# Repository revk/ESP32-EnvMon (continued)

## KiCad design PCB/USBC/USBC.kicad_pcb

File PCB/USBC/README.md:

# USBC

These files are for use in [KiCad](https://www.kicad.org).

## Trademark

This is an open source project, but bear in mind you cannot sell boards bearing the Andrews & Arnold Ltd name, the A&A logo, the registered trademark AJK logo, or the GS1 allocated EANs assigned to Andrews & Arnold Ltd.

## Images

*Auto generated 2025-05-04T08:07:17*

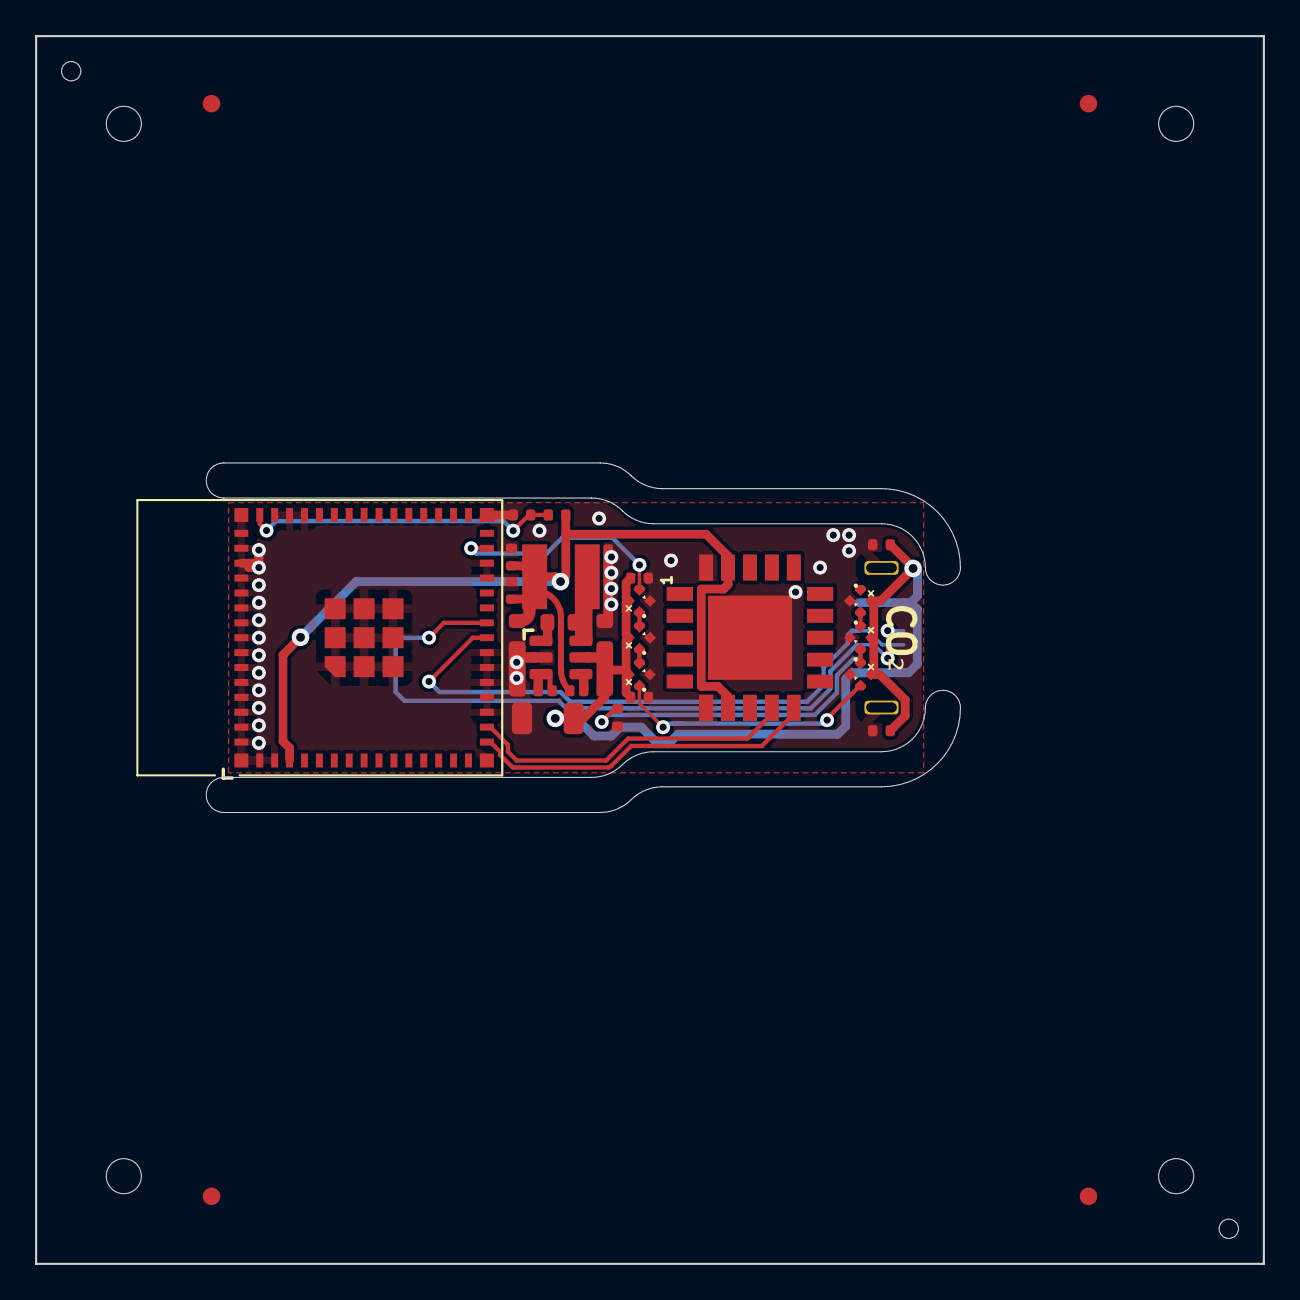
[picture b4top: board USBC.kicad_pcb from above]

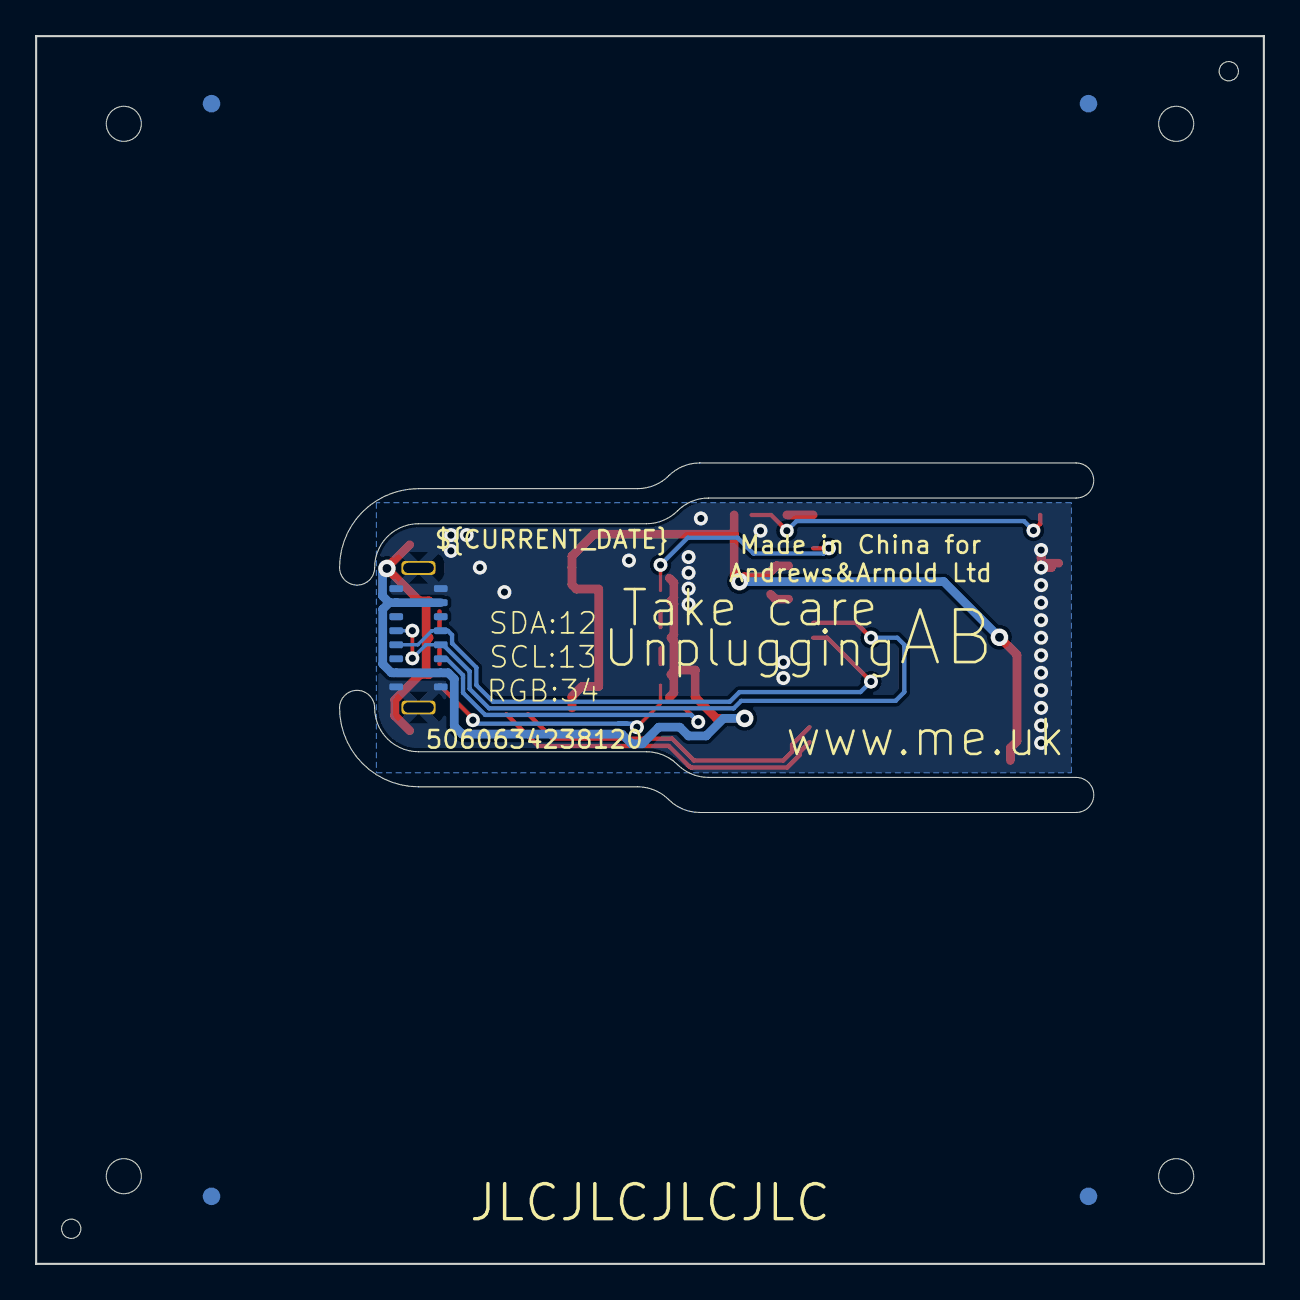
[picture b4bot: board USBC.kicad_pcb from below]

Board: 2 copper layers, 70.0 x 70.0 mm, 30 parts (2 on the bottom side), 15 nets.

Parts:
C1, C4, C5, C9, C11: 100nF; C_0402
C2: 22uF; C_0402
C3: 1uF; C_0402
C6: 10uF 35V; C_0603_
C7: 10uF 6.3V; C_0603_
C8: 100nF; C_0603_
C10: 100uF 6.3V; C_1206
D1, D2, D3, D4, D5, D6: XL-1010RGBC-WS2812B; SMD1010
J1: USB-C-Plug-V
L2: 10uH; L_4x4_
PCB1: 70x70; PCB7070
R1: 10K; R_0402
R2: 5K1; R_0402
R9: 124k; R_0402_
R10: 39k2; R_0402_
R11: 1M; R_0402_
U2: ESP32-S3-MINI-1
U3: SCD41-D-R1; SCD41
U5: MD8942; SOT-23-6-MD8942
V1, V2: 70; VCUT70N

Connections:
+3.3V: C1.1, C2.1, R1.1, U2.3 (3V3), U3.7 (VDD), U3.19 (VDDH), U5.8 (VOUT)
D+: J1.A6 (D+), J1.B6 (D+), U2.24 (GPIO20)
D-: J1.A7 (D-), J1.B7 (D-), U2.23 (GPIO19)
GND: C1.2, C2.2, C3.2, C4.2, C5.2, C9.2, C10.1, C11.2, D1.3 (-), D2.3 (-), D3.3 (-), D4.3 (-), D5.3 (-), D6.3 (-), J1.A1 (GND), J1.A12 (GND), J1.B1 (GND), J1.B12 (GND), J1.S1 (SHIELD), J1.S2 (SHIELD), R2.2, U2.1 (GND), U2.2 (GND), U2.18 (GPIO14), U2.19 (GPIO15), U2.20 (GPIO16), U2.21 (GPIO17), U2.22 (GPIO18), U2.27 (GPIO47), U2.28 (GPIO33), U2.42 (GND), U2.43 (GND), U2.44 (GPIO46), U2.46 (GND), U2.47 (GND), U2.48 (GND), U2.49 (GND), U2.50 (GND), U2.51 (GND), U2.52 (GND), U2.53 (GND), U2.54 (GND), U2.55 (GND), U2.56 (GND), U2.57 (GND), U2.58 (GND), U2.59 (GND), U2.60 (GND), U2.61 (GND), U2.62 (GND), U2.63 (GND), U2.64 (GND), U2.65 (GND), U3.6 (GND), U3.20 (GND), U3.21 (GND), U5.2 (GND), U5.7 (GND)
LED: D1.4 (I), U2.29 (GPIO34)
unnamed: D1.1 (O), D2.4 (I)
unnamed: D2.1 (O), D3.4 (I)
unnamed: D3.1 (O), D4.4 (I)
unnamed: D4.1 (O), D5.4 (I)
unnamed: D5.1 (O), D6.4 (I)
unnamed: J1.A5 (CC), R2.1
unnamed: C3.1, R1.2, U2.45 (EN)
SCL: U2.17 (GPIO13), U3.9 (SCL)
SDA: U2.16 (GPIO12), U3.10 (SDA)
VBUS: C4.1, C5.1, C9.1, C10.2, C11.1, D1.2 (+), D2.2 (+), D3.2 (+), D4.2 (+), D5.2 (+), D6.2 (+), J1.A4 (VBUS), J1.A9 (VBUS), J1.B4 (VBUS), J1.B9 (VBUS), U5.5 (VIN)

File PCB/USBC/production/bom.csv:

Designator,Footprint,Quantity,Value,LCSC Part #
"C1, C11, C4, C5, C9",C_0402,5,100nF,
C10,C_1206,1,100uF 6.3V,
C2,C_0402,1,22uF,
C3,C_0402,1,1uF,
C6,C_0603_,1,10uF 35V,C194427
C7,C_0603_,1,10uF 6.3V,C1691
C8,C_0603_,1,100nF,
"D1, D2, D3, D4, D5, D6",SMD1010,6,XL-1010RGBC-WS2812B,C5349953
J1,USB-C-Plug-V,1,USB-C-Plug-V,C399938
L2,L_4x4_,1,10uH,
R1,R_0402,1,10K,
R10,R_0402_,1,39k2,
R11,R_0402_,1,1M,
R2,R_0402,1,5K1,
R9,R_0402_,1,124k,
U2,ESP32-S3-MINI-1,1,ESP32-S3-MINI-1,C3013941
U3,SCD41,1,SCD41-D-R1,
U5,SOT-23-6-MD8942,1,MD8942,C2684786

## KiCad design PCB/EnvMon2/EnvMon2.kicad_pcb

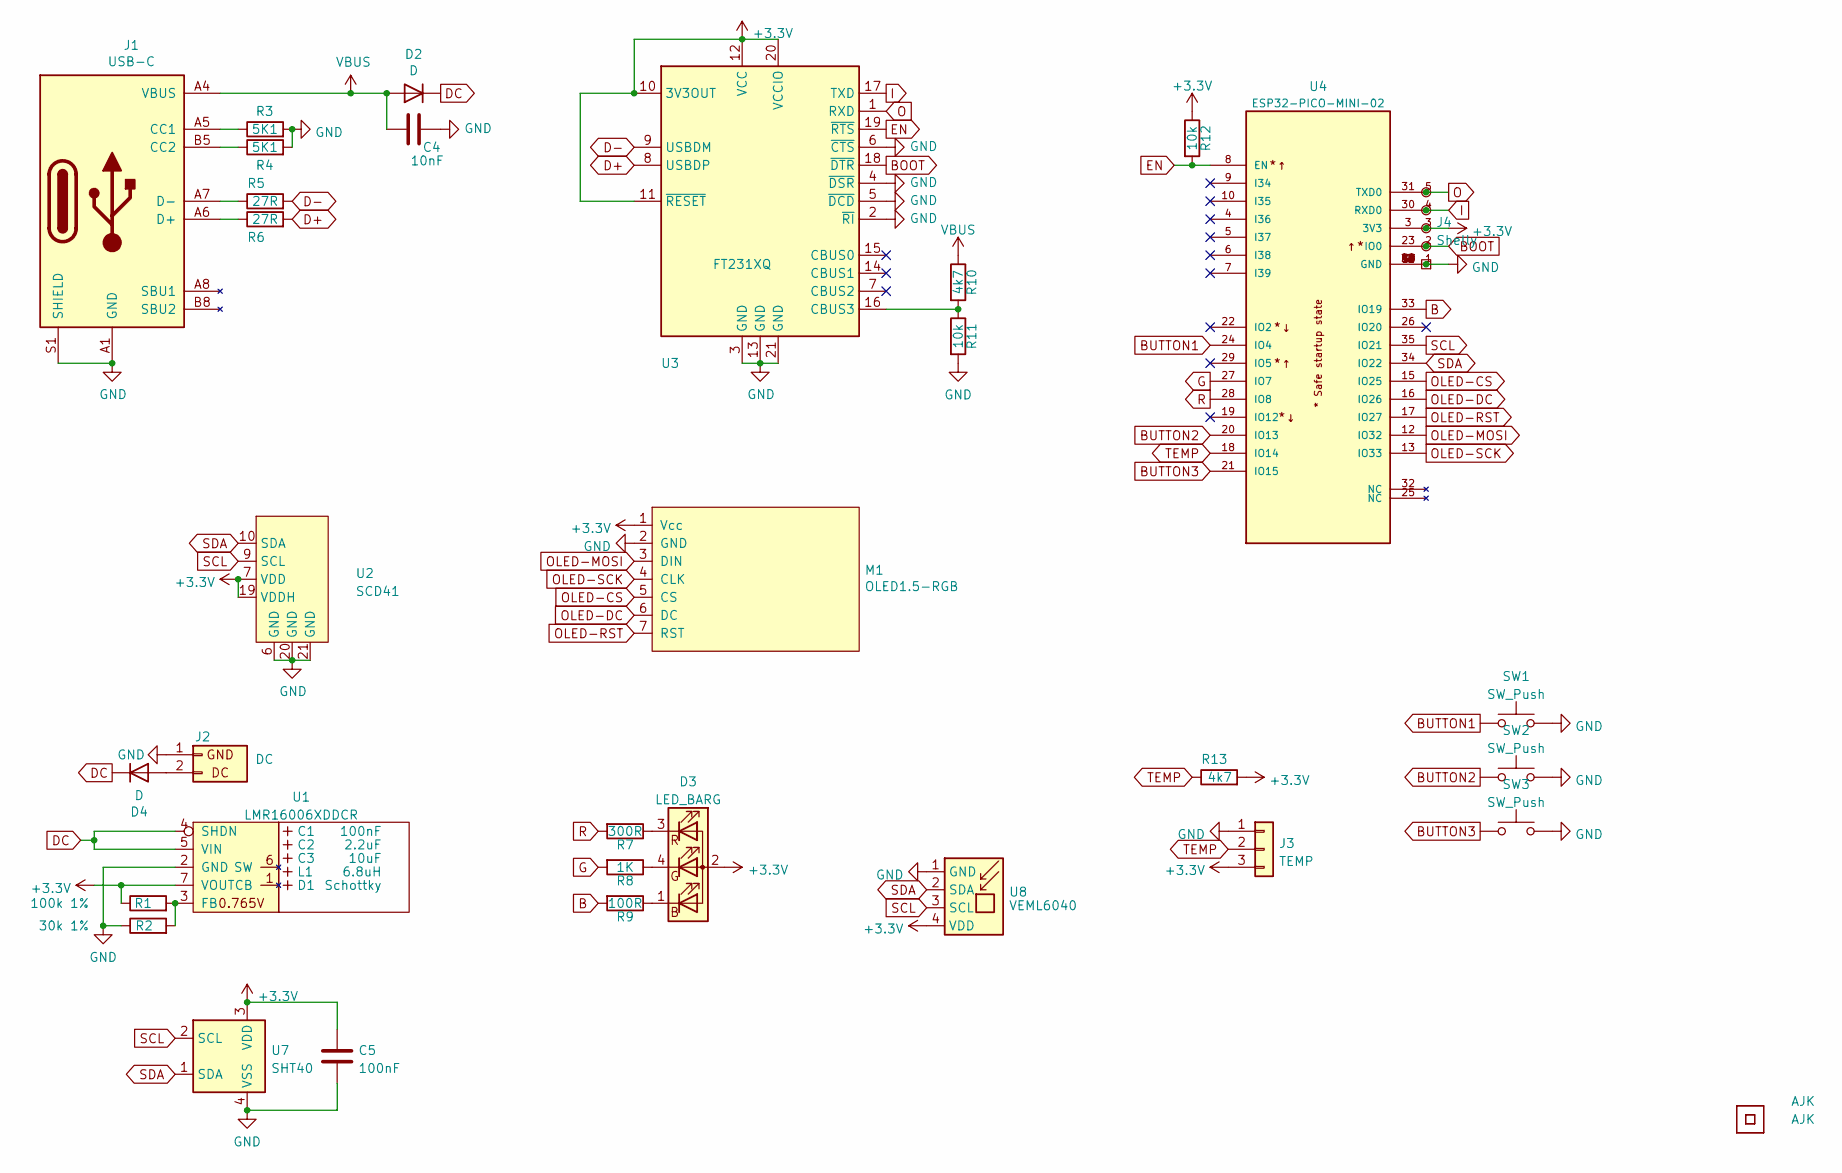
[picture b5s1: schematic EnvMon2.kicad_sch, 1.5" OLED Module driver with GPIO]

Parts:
C1: 100nF; C_0603_; LCSC Part # C30926
C2: 2.2uF; C_0805_; LCSC Part # C19110
C3: 10uF; C_0805_; LCSC Part # C17024
C4: 10nF; C_0603
C5: 100nF; C_0603
D1: Schottky; D_1206_; LCSC Part # C143805
D2, D4: D; D_1206; LCSC Part # C143805
D3: LED_BARG; MHS190RGBCT; LCSC Part # C409798
J1: USB-C; USC16-TR; LCSC Part # C709357
J2: DC; PTSM-HH-2-RA-W
J3: TEMP; PTSM-HH-3-RA
J4: Shelly
L1: 6.8uH; L_4x4_; LCSC Part # C354575
Logo1, Logo2: AJK
M1: OLED1.5-RGB
R1: 100k 1%; R_0603; LCSC Part # C14675
R2: 30k 1%; R_0603; LCSC Part # C100001
R3, R4: 5K1; R_0603
R5, R6: 27R; R_0603
R7: 300R; R_0603
R8: 1K; R_0603
R9: 100R; R_0603
R10, R13: 4k7; R_0603
R11, R12: 10k; R_0603
SW1, SW2, SW3: SW_Push; SW_PUSH_6mm_H13mm
U1: LMR16006XDDCR; SOT-23-Thin-6-Reg; Part No LMR16006XDDCR; LCSC Part # C87080
U2: SCD41
U3: FT231XQ; QFN-20-1EP_4x4mm_P0.5mm_EP2.5x2.5mm; JLCPCB Rotation Offset -90
U4: ESP32-PICO-MINI-02; PARTREV v1.0; LCSC Part # C2980306
U5: QR; QR-ENVMON
U7: SHT40; Sensirion_DFN-4_1.5x1.5mm_P0.5mm_SHT4x; LCSC Part # C2909890
U8: VEML6040; LCSC Part # C78465

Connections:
+3.3V: C5.1, D3.2 (A), J3.3, J4.3 (3V3), M1.1 (Vcc), R1.1, R12.1, R13.2, U1.7 (VOUT), U2.7 (VDD), U2.19 (VDDH), U3.10 (3V3OUT), U3.11 (~RESET), U3.12 (VCC), U3.20 (VCCIO), U4.3 (3V3), U7.3 (VDD), U8.4 (VDD)
B: R9.2, U4.33 (IO19)
BOOT: J4.2 (0), U3.18 (~DTR), U4.23 (IO0)
BUTTON1: SW1.1, U4.24 (IO4)
BUTTON2: SW2.1, U4.20 (IO13)
BUTTON3: SW3.1, U4.21 (IO15)
D+: R6.2, U3.8 (USBDP)
D-: R5.2, U3.9 (USBDM)
DC: D2.1 (K), D4.1 (K), U1.4 (SHDN), U1.5 (VIN)
EN: R12.2, U3.19 (~RTS), U4.8 (EN)
G: R8.2, U4.27 (IO7)
GND: C4.1, C5.2, J1.A1 (GND), J1.A12 (GND), J1.B1 (GND), J1.B12 (GND), J1.S1 (SHIELD), J2.1 (GND), J3.1, J4.1 (GND), M1.2 (GND), R2.1, R3.2, R4.2, R11.2, SW1.2, SW2.2, SW3.2, U1.2 (GND), U2.6 (GND), U2.20 (GND), U2.21 (GND), U3.2 (~RI), U3.3 (GND), U3.4 (~DSR), U3.5 (~DCD), U3.6 (~CTS), U3.13 (GND), U3.21 (GND), U4.1 (GND), U4.2 (GND), U4.11 (GND), U4.14 (GND), U4.36 (GND), U4.37 (GND), U4.38 (GND), U4.39 (GND), U4.40 (GND), U4.41 (GND), U4.42 (GND), U4.43 (GND), U4.44 (GND), U4.45 (GND), U4.46 (GND), U4.47 (GND), U4.48 (GND), U4.49 (GND), U4.50 (GND), U4.51 (GND), U4.52 (GND), U4.53 (GND), U7.4 (VSS), U8.1 (GND)
I: J4.4 (Rx), U3.17 (TXD), U4.30 (RXD0)
unnamed: D3.1 (BK), R9.1
unnamed: D3.4 (GK), R8.1
unnamed: D3.3 (RK), R7.1
unnamed: D4.2 (A), J2.2 (DC)
unnamed: J1.A5 (CC1), R3.1
unnamed: J1.B5 (CC2), R4.1
unnamed: J1.A6 (D+), J1.B6 (D+), R6.1
unnamed: J1.A7 (D-), J1.B7 (D-), R5.1
unnamed: R1.2, R2.2, U1.3 (FB)
unnamed: R10.2, R11.1, U3.16 (CBUS3)
O: J4.5 (Tx), U3.1 (RXD), U4.31 (TXD0)
OLED-CS: M1.5 (CS), U4.15 (IO25)
OLED-DC: M1.6 (DC), U4.16 (IO26)
OLED-MOSI: M1.3 (DIN), U4.12 (IO32)
OLED-RST: M1.7 (RST), U4.17 (IO27)
OLED-SCK: M1.4 (CLK), U4.13 (IO33)
R: R7.2, U4.28 (IO8)
SCL: U2.9 (SCL), U4.35 (IO21), U7.2 (SCL), U8.3 (SCL)
SDA: U2.10 (SDA), U4.34 (IO22), U7.1 (SDA), U8.2 (SDA)
TEMP: J3.2, R13.1, U4.18 (IO14)
VBUS: C4.2, D2.2 (A), J1.A4 (VBUS), J1.A9 (VBUS), J1.B4 (VBUS), J1.B9 (VBUS), R10.1

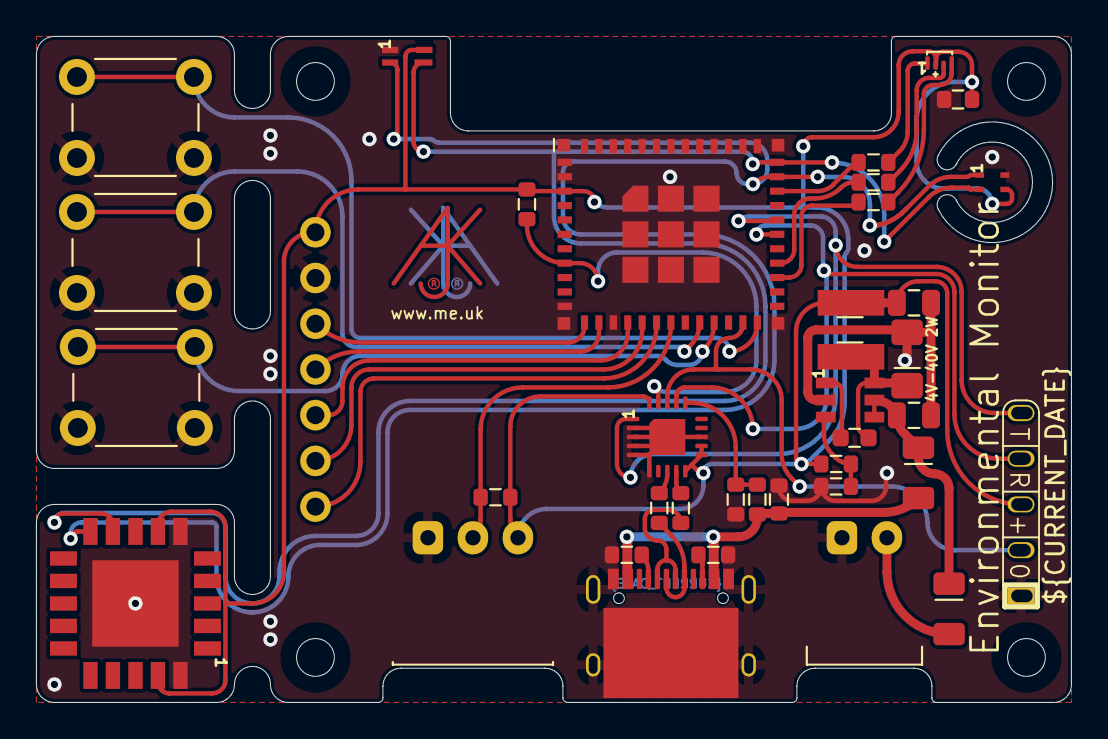
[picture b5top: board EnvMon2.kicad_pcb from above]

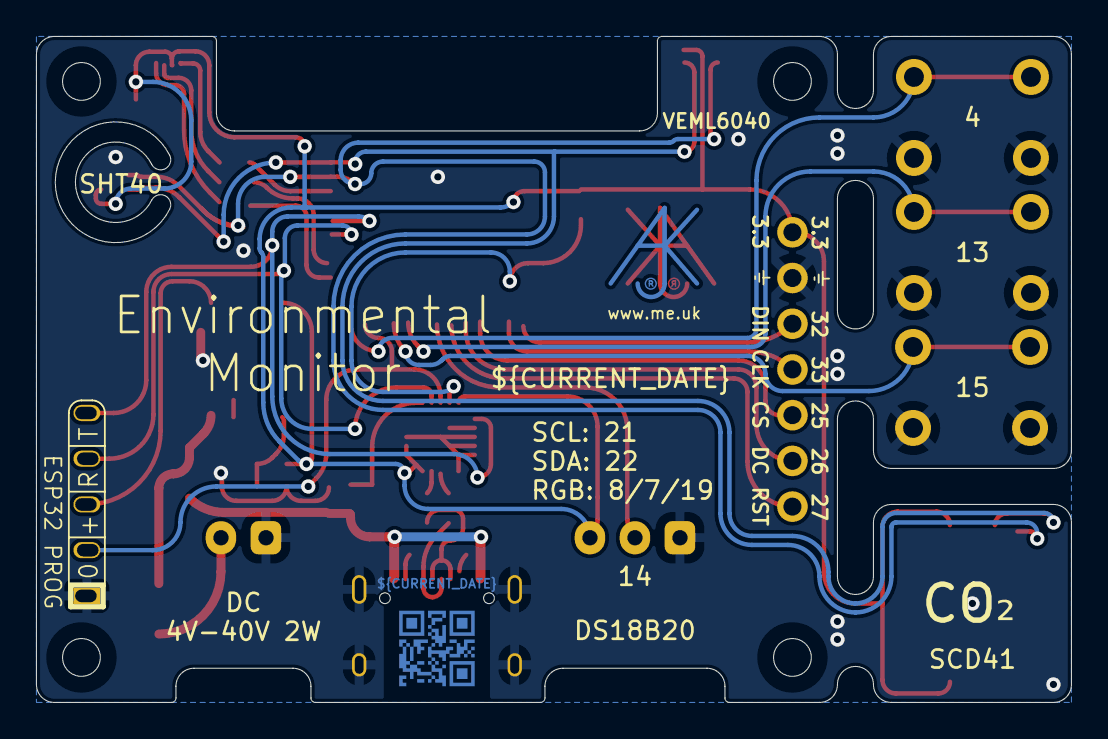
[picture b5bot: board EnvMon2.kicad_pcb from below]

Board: 2 copper layers, 57.5 x 37.0 mm, 40 parts (2 on the bottom side), 34 nets.

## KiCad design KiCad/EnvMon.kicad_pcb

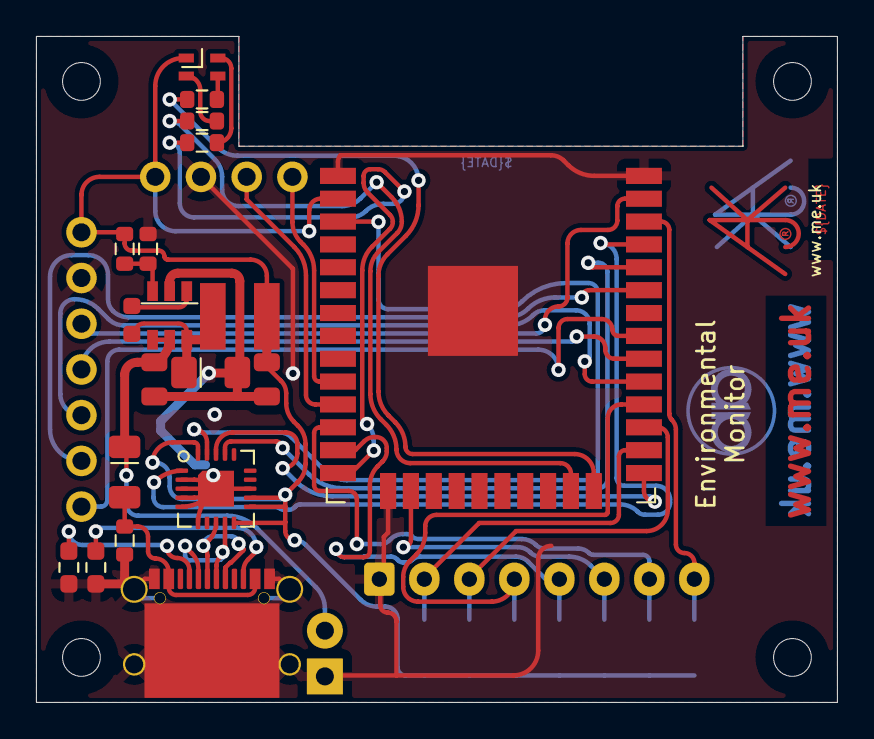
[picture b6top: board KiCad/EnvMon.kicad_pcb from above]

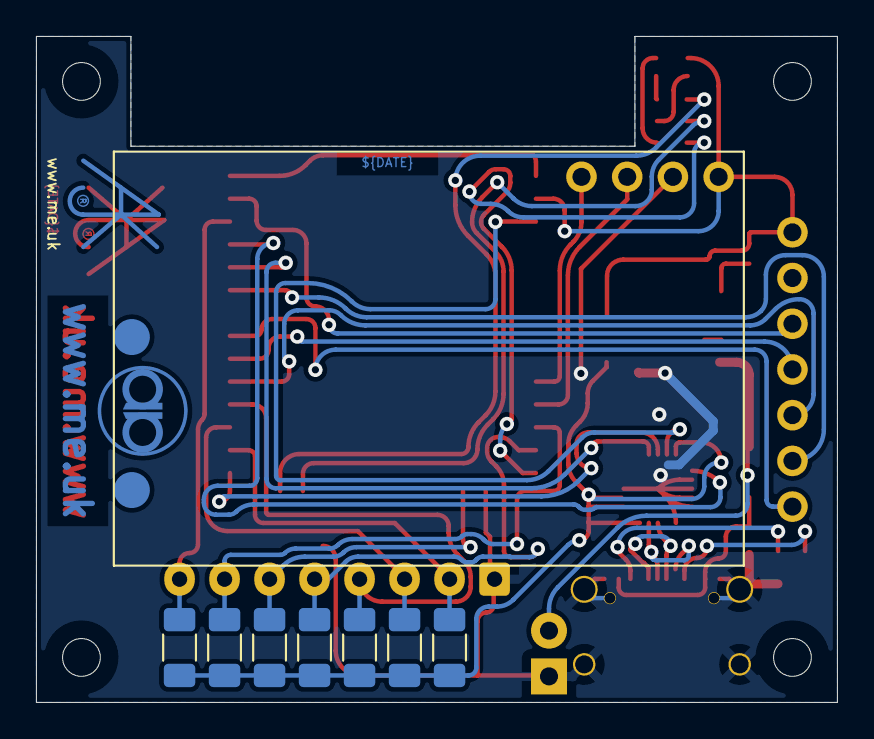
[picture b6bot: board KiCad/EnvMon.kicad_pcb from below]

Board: 2 copper layers, 44.5 x 37.0 mm, 33 parts (11 on the bottom side), 33 nets.

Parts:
C1: 0.1uF; Hidden
C2: 2.2uF; Hidden
C3: 10uF; Hidden
C4: 10nF; C_0603
D1: Schottky; Hidden
D2: D; D_1206
D3: RGB; LED-RGB-1.6x1.6
J1: USB-C; USC16-TR-Round
J2: DC
J3: GPIO; Molex_MiniSPOX_H8RA
L1: 6.8uH; Hidden
Logo1: AA
Logo2, Logo3: AJK
M1: SCD30-4pin
M2: OLED1.5-RGB
R1: 100k 1% or 0R; R_0603
R2: 30k 1% or NF; R_0603
R3, R4: 5K1; R_0603_1608Metric_Pad0.98x0.95mm_HandSolder
R5: 732R; R_0603
R6: 2K; R_0603
R7: 324R; R_0603
R8, R9, R10, R11, R12, R13, R14: NF; R_1206_3216Metric_Pad1.30x1.75mm_HandSolder
U1: LMR16006+FB; RegulatorBlockFB
U2: FT231XQ; QFN-20-1EP_4x4mm_P0.5mm_EP2.5x2.5mm
U3: ESP32-WROOM-32

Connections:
+3V3: D3.1 (A), M1.1 (VDD), M2.1 (Vcc), R1.1, R8.2, R9.2, R10.2, R11.2, R12.2, R13.2, R14.2, U1.4 (VOUT), U2.10 (3V3OUT), U2.11 (~RESET), U2.12 (VCC), U2.20 (VCCIO), U3.2 (VDD)
B: R7.2, U3.23 (IO15)
CO2-SCL: M1.3 (TX/SCL), U3.11 (IO26)
CO2-SDA: M1.4 (RX/SDA), U3.10 (IO25)
DC: D2.1 (K), J2.2 (DC), U1.1 (SHDN), U1.2 (VIN)
G: R6.2, U3.24 (IO2)
GND: C4.1, J1.A1 (GND), J1.A12 (GND), J1.B1 (GND), J1.B12 (GND), J1.S1 (SHIELD), J2.1 (GND), J3.1, M1.2 (GND), M2.2 (GND), R2.1, R3.2, R4.2, U1.3 (GND), U2.2 (~RI), U2.3 (GND), U2.4 (~DSR), U2.5 (~DCD), U2.6 (~CTS), U2.13 (GND), U2.21 (GND), U3.1 (GND), U3.15 (GND), U3.38 (GND), U3.39 (GND)
IO1: J3.2, R8.1, U3.26 (IO4)
IO2: J3.3, R9.1, U3.27 (IO16)
IO3: J3.4, R10.1, U3.28 (IO17)
IO4: J3.5, R11.1, U3.13 (IO14)
IO5: J3.6, R12.1, U3.16 (IO13)
IO6: J3.7, R13.1, U3.12 (IO27)
IO7: J3.8, R14.1, U3.36 (IO22)
unnamed: D3.2 (RK), R5.1
unnamed: D3.3 (GK), R6.1
unnamed: D3.4 (BK), R7.1
unnamed: J1.A5 (CC1), R4.1
unnamed: J1.A6 (D+), J1.B6 (D+), U2.8 (USBDP)
unnamed: J1.A7 (D-), J1.B7 (D-), U2.9 (USBDM)
unnamed: J1.B5 (CC2), R3.1
unnamed: R1.2, R2.2, U1.5 (FB)
unnamed: U2.1 (RXD), U3.35 (TXD0/IO1)
unnamed: U2.17 (TXD), U3.34 (RXD0/IO3)
unnamed: U2.18 (~DTR), U3.25 (IO0)
unnamed: U2.19 (~RTS), U3.3 (EN)
OLED-CS0: M2.5 (CS), U3.29 (IO5)
OLED-DC: M2.6 (DC), U3.33 (IO21)
OLED-MOSI: M2.3 (DIN), U3.37 (IO23)
OLED-RST: M2.7 (RST), U3.31 (IO19)
OLED-SCLK: M2.4 (CLK), U3.30 (IO18)
R: R5.2, U3.14 (IO12)
VBUS: C4.2, D2.2 (A), J1.A4 (VBUS), J1.A9 (VBUS), J1.B4 (VBUS), J1.B9 (VBUS)

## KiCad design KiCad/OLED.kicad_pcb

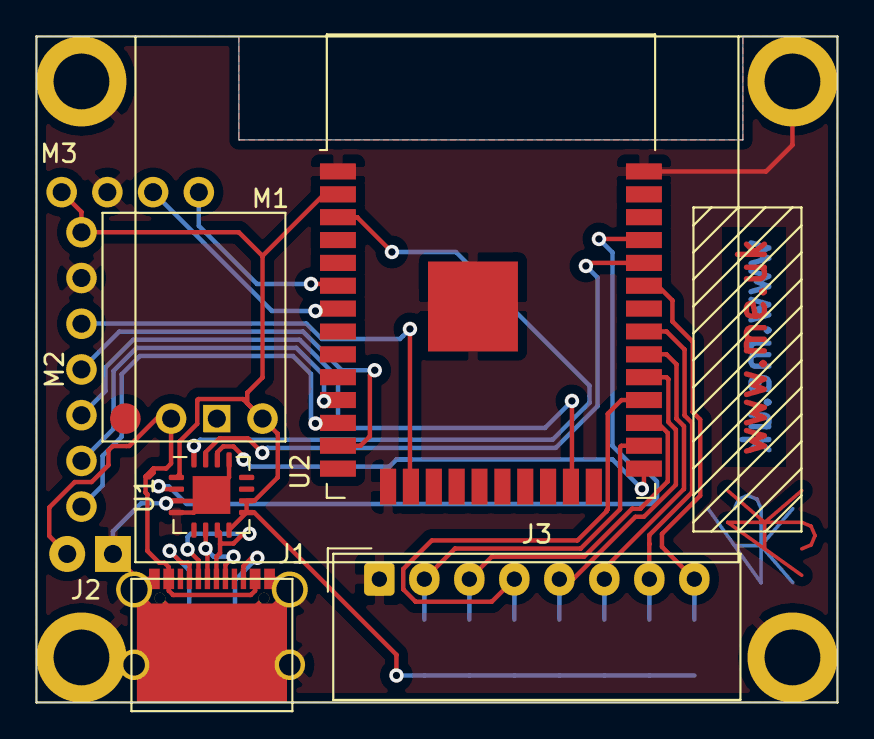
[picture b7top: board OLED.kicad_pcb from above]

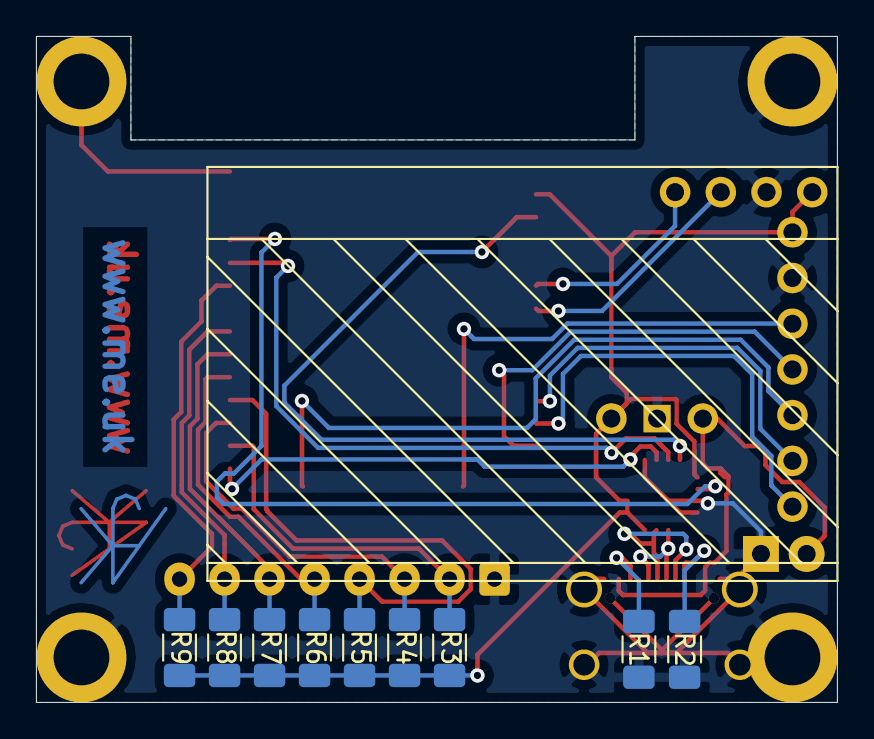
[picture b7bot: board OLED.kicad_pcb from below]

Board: 2 copper layers, 44.5 x 37.0 mm, 17 parts (10 on the bottom side), 25 nets.

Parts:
J1: USB-C; USC16-TR-Round
J2: DC
J3: GPIO; Molex_SPOX_5268-08A_1x08_P2.50mm_Horizontal
M1: D24V5F3-NoSHDN
M2: OLED1.5-RGB
M3: SCD30-4pin
R1, R2: 5K1; R_1206_3216Metric_Pad1.30x1.75mm_HandSolder
R3, R4, R5, R6, R7, R8, R9: NF; R_1206_3216Metric_Pad1.30x1.75mm_HandSolder
U1: FT230XQ; QFN-16-1EP_4x4mm_P0.65mm_EP2.1x2.1mm
U2: ESP32-WROOM-32

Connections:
+3V3: M1.4, M2.1, M3.1, R3.2, R4.2, R5.2, R6.2, R7.2, R8.2, R9.2, U1.1, U1.8, U1.9, U1.10, U2.2
CO2-SCL: M3.3, U2.7
CO2-SDA: M3.4, U2.6
GND: J1.A1, J1.A12, J1.B1, J1.B12, J1.S1, J2.1, J3.1, M1.3, M2.2, M2.S, M3.2, R1.2, R2.2, U1.3, U1.4, U1.13, U1.17, U2.1, U2.15, U2.38, U2.39
IO1: J3.2, R3.1, U2.26
IO2: J3.3, R4.1, U2.27
IO3: J3.4, R5.1, U2.28
IO4: J3.5, R6.1, U2.29
IO5: J3.6, R7.1, U2.30
IO6: J3.7, R8.1, U2.31
IO7: J3.8, R9.1, U2.33
unnamed: J1.A4, J1.A9, J1.B4, J1.B9, J2.2, M1.2
unnamed: J1.A5, R2.1
unnamed: J1.A6, J1.B6, U1.6
unnamed: J1.A7, J1.B7, U1.7
unnamed: J1.B5, R1.1
unnamed: U1.2, U2.35
unnamed: U1.14, U2.25
unnamed: U1.15, U2.34
unnamed: U1.16, U2.3
OLED-CS0: M2.5, U2.23
OLED-DC: M2.6, U2.11
OLED-MOSI: M2.3, U2.16
OLED-RST: M2.7, U2.12
OLED-SCLK: M2.4, U2.13

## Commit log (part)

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2023-01-29 Notes
2023-02-05 Web config / status
2023-02-05 Added builds
2023-02-06 webcontrol
2023-02-06 Library update
2023-02-06 New builds
2023-02-10 Log BlueCoinT app too
2023-02-15 More testing needed
2023-02-15 Config
2023-02-15 Maybe
2023-02-15 Tidy
2023-02-15 Display T
2023-03-10 Try countdown
2023-03-10 New bin
2023-03-10 No .bin
2023-03-11 Tweak defaults
2023-03-11 Updated sql lib
2023-03-11 Clock at night
2023-03-12 New clock and new countdown
2023-03-12 New countdown
2023-03-13 Clock
2023-03-20 Free
2023-03-21 Changed to HA if HA seen
2023-03-21 Back as HA being a config
2023-03-26 Local time
2023-04-05 Tweak connectors
2023-04-15 Daikin-Faikin rename
2023-04-16 issue
2023-04-16 Update build
2023-04-16 Build
2023-04-29 New PCB with Sensitron SHT40 on board
2023-04-29 Added SHT40
2023-04-29 Started EnvHT
2023-04-29 Started SHT logic
2023-04-29 Tracked EnvHT
2023-05-01 Tody
2023-05-12 Tidy 3d
2023-05-12 Screw adjust
2023-05-12 Debug error
2023-05-12 Change default to match schematic
2023-05-12 Arg, no
2023-05-12 Tweak
2023-05-12 Screws
2023-05-12 Damn screws
2023-05-12 Cleanup
2023-05-13 Slight tweaks
2023-05-27 checkpoint
2023-05-27 release
2023-06-01 Cap chanmge
2023-06-12 Silkscreen
2023-06-18 Silk
2023-06-18 Silk and change VEML
2023-06-22 popt changes
2023-06-27 VEML6040
2023-08-10 S3 board basic tracking started
2023-08-10 Some work on new libraries
2023-08-10 Not working on S3
2023-08-10 Pretty tracks
2023-08-11 Work in progress
2023-08-11 DS18B20 removed, to be added back with new library
2023-08-11 New DS18B20
2023-08-11 Some progress
2023-08-11 CONFIG_ESP_TASK_WDT_PANIC
2023-08-12 One board
2023-08-19 New reg
2023-08-31 New design 3D case
2023-09-01 Stupid sql, this is way faster
2023-09-03 "rh" on BLE
2023-09-04 Library change
2023-09-06 Fix scale issue
2023-10-08 Fix ds18b20
2023-10-09 Simpler flush case
2023-10-09 Include in build
2023-10-15 WS2812B LED
2023-12-19 Start new PCB
2023-12-19 blind s3
2023-12-19 neater
2023-12-27 Clear defaults and fix ilk
2023-12-27 WS2812
2023-12-27 Pull down
2023-12-29 forma
2023-12-29 backoff
2023-12-30 More LEDs
2023-12-30 USBC case done
2023-12-30 Case
2024-08-11 New plugs
2024-09-16 Cleaner makefile
2024-09-17 Moved to new settings system
2024-09-17 Beta releases
2024-09-17 Beta
2024-09-17 Close... Tidied for settings.def
2024-09-17 Settings (still needs logo)
2024-09-17 Logo
2024-09-17 Rework new settings lib and updated librarty
2024-09-18 Testing icon tracking
2024-09-18 Library update fixed the issue
2024-09-18 icon in data report
2024-09-23 Testing HA logic
2024-09-23 HA improvements
2024-09-24 CO2 LEDs
2024-09-24 Better controls
2024-09-24 New HA lib
2024-09-24 Back
2024-10-10 Leading 0
2024-11-12 LED tweaks
2024-11-13 appprefix
2024-12-20 Temp offset logic
2025-01-01 Latest tas does 1PM other way?!
2025-01-01 OK finally
2025-01-23 PCB Update
2025-03-12 a/c status
2025-03-26 Updated for gfx and settings
2025-04-13 Started Env2
2025-04-13 Tracked and SS
2025-04-13 Tracking
2025-04-13 Render
2025-04-14 Tweaks and render
2025-04-14 Pressure sensor
2025-04-14 Silk screen
2025-04-20 New board
2025-04-20 Tidy up
2025-04-21 Render button
2025-04-24 As ordered
2025-04-25 Moved to FaikinRemote project
2025-04-25 New case work
2025-04-26 Reworked case
2025-04-27 New case options
2025-04-28 Top cover
2025-04-28 Tidy new case cover
2025-05-03 Reworked 3D
2025-05-03 envmon for remote
2025-05-03 Try again
2025-05-03 Log heat/fan
2025-05-03 Space for leads
2025-05-04 Reworked
2025-05-04 Fitting
2025-05-05 More cases
2025-05-06 Target
2025-05-06 Revert
2025-06-09 D'Oh
2025-09-10 Fixed GPIO
2025-09-10 IR added, and more DS18B20
2025-09-10 More DS18B20, needs some work I expect
2025-10-10 New LEDs
